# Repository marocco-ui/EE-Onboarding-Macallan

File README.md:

# Basic sensor interface PCB

EE subteam onboarding project. A 2-layer, 60 × 60 mm board that reads one 0 to 3.3 V analog sensor and one pushbutton with an ESP32-S3, powered and programmed over USB-C.

Calculations for the regulator, LED resistor, power budget, and trace widths are in `calculations.md`.

## Deliverables

| Item | File |
|---|---|
| Editable KiCad project | `kicad bike project.kicad_pro`, `.kicad_sch`, `.kicad_pcb`, `.kicad_dru` |
| Schematic PDF | `exports/schematic.pdf` |
| PCB layout PDF (one page per layer) | `exports/board_layout.pdf` |
| PCB layout screenshots | `board_preview.png`, `exports/board_top.png`, `exports/board_bottom.png` |
| Required calculations | `calculations.md` |
| Design decisions | this README |
| Checks | `ERC 3.rpt` (0 errors, 0 warnings), `DRC 4.rpt` (0 violations, 0 unconnected, schematic parity clean) |

## Block diagram

    USB-C (J1) --5 V--> AP7361C LDO (U2) --3.3 V--> ESP32-S3-WROOM-1 (U1)
        |                                               |
        +---- D+ / D- (native USB) ---------------------+
                                                         |
    Sensor connector (J2) --> divider + RC filter --> GPIO1 (ADC1_CH0)
    User button (SW1) --> pull-up + RC debounce --> GPIO4
    BOOT (SW2) --> GPIO0      RESET (SW3) --> EN

## Design decisions

**Microcontroller.** ESP32-S3-WROOM-1-N8 (8 MB flash, no PSRAM). It has native USB, so one USB-C port handles power and programming with no USB-to-serial chip. It also has an official KiCad symbol and footprint, which removes the risk of a hand-drawn footprint. The ESP32-C3-MINI-1 was the first choice, but KiCad's library has neither for it.

**Power.** 5 V comes from USB-C VBUS. CC1 and CC2 each get their own 5.1 kΩ pull-down (R8, R9), which tells a USB-C charger or port to turn on 5 V. The AP7361C LDO drops it to 3.3 V. An LDO fits because the load is under 0.5 A and the drop is only 1.7 V. See `calculations.md` for the heat check.

**Programming.** GPIO19 and GPIO20 are the chip's USB D− and D+. Both D+ pins on the USB-C connector are tied together, and both D− pins, so the cable works either way up. SW2 (BOOT) pulls GPIO0 low and SW3 (RESET) pulls EN low. Holding BOOT while tapping RESET forces download mode if USB auto-reset ever fails.

**Strapping pins.** GPIO0, GPIO3, GPIO45, and GPIO46 are read at power-up.
- GPIO0: internal pull-up plus R2 (10 kΩ). High = run the program, low = download mode.
- GPIO3: no internal pull, and the datasheet says it must not float. R3 (10 kΩ) pulls it up.
- GPIO45 and GPIO46: internal pull-downs are the correct levels, so both are left open.
None of these are used for the sensor or button.

**Analog input.** The ESP32-S3 ADC reads 0 to 3.1 V at its highest attenuation, so a 0 to 3.3 V sensor would clip at the top. A 10 kΩ / 30 kΩ divider scales 3.3 V to 2.475 V, leaving margin for resistor tolerance. A 100 nF cap at the ADC pin filters noise above about 212 Hz. The sensor uses GPIO1 (ADC1_CH0) because ADC2 is shared with Wi-Fi and its reads can fail while Wi-Fi runs.

**Digital input.** SW1 on GPIO4 is active low: 10 kΩ pull-up, button to ground, 100 nF for a 1 ms debounce. GPIO4 is not a strapping pin, so holding the button at power-up can't change the boot mode.

**Indicator.** D1 is a green power LED on the 3.3 V rail with a 680 Ω resistor (about 2 mA). It confirms the regulator works.

## Pin assignments (U1, ESP32-S3-WROOM-1)

| Module pin | Signal | Connection |
|---|---|---|
| 2 | 3V3 | LDO output, C4 + C5 local decoupling |
| 1, 40, 41 (pad) | GND | Ground plane |
| 3 | EN | R1 10 kΩ to 3V3, C6 1 uF to GND, SW3 to GND |
| 27 | IO0 | BOOT: R2 10 kΩ pull-up, SW2 to GND |
| 15 | IO3 | R3 10 kΩ pull-up (strapping) |
| 39 | IO1 | Sensor signal after divider (ADC1_CH0) |
| 4 | IO4 | User button SW1 |
| 13 | IO19 | USB D− |
| 14 | IO20 | USB D+ |
| All others | NC | No-connect flags in the schematic |

## Parts list

| Ref | Value / part | KiCad footprint | Purpose |
|---|---|---|---|
| U1 | ESP32-S3-WROOM-1-N8 | RF_Module:ESP32-S3-WROOM-1 | Microcontroller |
| U2 | AP7361C-33E-13 | Package_TO_SOT_SMD:SOT-223-3_TabPin2 | 5 V to 3.3 V LDO |
| J1 | USB-C, USB 2.0, 16-pin (GCT USB4105-GF-A) | Connector_USB:USB_C_Receptacle_GCT_USB4105-xx-A_16P_TopMnt_Horizontal | Power and programming |
| J2 | JST PH 3-pin (3V3, SIG, GND) | Connector_JST:JST_PH_B3B-PH-K_1x03_P2.00mm_Vertical | Sensor connector |
| SW1, SW2, SW3 | Tactile switch | Button_Switch_SMD:SW_SPST_TL3342 | USER, BOOT, RESET |
| D1 | LTST-C191KGKT green LED | LED_SMD:LED_0603_1608Metric | Power indicator |
| R1, R2, R3, R7 | 10 kΩ | Resistor_SMD:R_0603_1608Metric | EN, strapping, and button pull-ups |
| R4 | 680 Ω | Resistor_SMD:R_0603_1608Metric | LED current limit |
| R5 | 10 kΩ 1 % | Resistor_SMD:R_0603_1608Metric | Divider top |
| R6 | 30 kΩ 1 % | Resistor_SMD:R_0603_1608Metric | Divider bottom |
| R8, R9 | 5.1 kΩ | Resistor_SMD:R_0603_1608Metric | USB-C CC pull-downs |
| C1 | 4.7 uF 10 V X5R | Capacitor_SMD:C_0805_2012Metric | LDO input |
| C2 | 100 nF | Capacitor_SMD:C_0603_1608Metric | LDO input bypass |
| C3 | 10 uF 10 V X5R | Capacitor_SMD:C_0805_2012Metric | LDO output |
| C4 | 22 uF 10 V X5R | Capacitor_SMD:C_0805_2012Metric | Module 3V3 bulk |
| C5 | 100 nF | Capacitor_SMD:C_0603_1608Metric | Module 3V3 bypass |
| C6 | 1 uF | Capacitor_SMD:C_0603_1608Metric | EN delay |
| C7 | 100 nF | Capacitor_SMD:C_0603_1608Metric | ADC filter |
| C8 | 100 nF | Capacitor_SMD:C_0603_1608Metric | Button debounce |
| H1 to H4 | M3 mounting hole | MountingHole:MountingHole_3.2mm_M3 | Mounting |

## Board layout

60 × 60 mm, 2 layers, fully routed. KiCad 10 DRC: 0 violations, 0 unconnected items, 0 schematic-parity issues.

- **Module (U1).** Centered on the top edge, antenna 0.3 mm inside the edge so its silkscreen stays on the board. KiCad's footprint carries an antenna keep-out on both layers. It blocks tracks, vias, pours, and parts in a 6 mm strip along the top edge.
- **Mounting holes.** The bottom pair sits 4 mm from each edge. The top pair sits 10 mm down, because the antenna keep-out covers the normal corner spot.
- **USB-C (J1).** Bottom edge, positioned on the footprint's "PCB Edge" mark. CC pull-downs R8 and R9 sit either side.
- **Power.** The AP7361C (U2) sits lower left with its input facing J1. C1 and C2 are at the input and C3 at the output. The power LED (D1, R4) is on the left edge.
- **Module support.** C5 and C4 sit next to module pins 1 and 2 (GND, 3V3). The EN parts (R1, C6) and button parts (R7, C8) form a column on the left. RESET (SW3) and USER (SW1) are on the left edge.
- **Sensor.** Divider R5, R6, and C7 sit right next to GPIO1 (pin 39). J2 is on the right edge, silkscreen-labeled 3V3 / SIG / GND. BOOT (SW2) and its pull-up R2 are on the right side near GPIO0 (pin 27).
- **Ground.** The bottom layer has a GND pour, tied to the USB-C shield, J2 pin 3, and the module's ground-pad vias.
- **Silkscreen.** Every label sits clear of copper, other silkscreen, and the board edge. Pin labels on J2 read 3V3 / SIG / GND, and the connectors and buttons are labeled USB 5V, SENSOR, RESET, USER, and BOOT.

### Net classes

| Class | Nets | Track | Via |
|---|---|---|---|
| Power | VBUS, +3V3 | 0.4 mm | 0.8 mm / 0.4 mm drill |
| Ground | GND | 0.3 mm | 0.6 mm / 0.3 mm drill |
| Default | everything else | 0.2 mm | 0.6 mm / 0.3 mm drill |

The first plan was 0.5 mm for power. That width could not reach the USB-C VBUS pins or squeeze past the regulator and the passives beside the module, so the router left those connections open. 0.4 mm still carries 1.2 A by IPC-2221, 3.4 times the 357 mA worst case (see `calculations.md`).

### DRC exceptions (`kicad bike project.kicad_dru`)

Both come from the official KiCad land patterns, not from the layout:

1. U1's exposed ground pad has 0.2 mm thermal vias. The board minimum is 0.3 mm, so the rule allows 0.2 mm for pads inside U1 only.
2. J1's alignment holes sit 0.19 mm from its GND pads. The board minimum is 0.25 mm, so the rule allows 0.15 mm inside J1 only.

### Routing

Routed with Freerouting 2.1 and checked with KiCad's DRC after every attempt. Ten variants were tried with different widths, via costs, and strategies. The final board is the cleanest: 27 vias, about 345 mm of top-layer track, and nothing left unrouted.

Before the autorouter ran, three things were drawn by hand and locked:

1. **USB D+ and D−.** Both pairs of connector pads are tied on the top layer, D+ just above the pad row and D− just below it, with no vias. From there the two lines run up together and turn 45° as a parallel pair into module pins 13 and 14.
2. **One 3.3 V crossing under the USB pair.** 3.3 V has to reach R2, R3, and J2 on the right of the USB pair. It crosses on the bottom layer with a 3.9 mm hop just below the module, at right angles to the USB lines. That keeps the ground pour under the USB pair almost unbroken.
3. **Ground as a plane.** GND was given to the router as the bottom-layer plane, so every top-side ground pad drops straight down through its own via.

What is on the bottom layer besides the ground pour:

- the 3.3 V hop under the USB pair, plus a 3.3 V run under the module's bottom edge out to R2 and J2
- two short hops on the left edge for EN and BUTTON out to the RESET and USER switches

These come from the placement. The 3.3 V pads and the EN and BUTTON pads alternate down the column beside the module, so something has to cross. None of these tracks runs under the USB lines.

## How the scripts work

The schematic and the first board layout were generated by Python scripts rather than drawn by hand, then finished and checked in KiCad 10. Each script is short and does one job. They run on KiCad's Python module (`pcbnew`, KiCad 7 or later) and need Java 21 for Freerouting.

| Step | Script | What it does |
|---|---|---|
| 1. Read the library | `tools/sexp.py`, `tools/extract.py` | KiCad files are plain-text s-expressions (nested parentheses). These read the official symbol library and pull out each part's pins and their positions. |
| 2. Draw the schematic | `tools/gen_sch.py` | Places every symbol, draws a short wire from each pin to a net label or power symbol, adds no-connect flags, and writes `kicad bike project.kicad_sch`. |
| 3. Check the connections | `tools/check_net.py` | Has KiCad export the netlist, then compares every net against the intended connection table. It passed on all 14 nets before the file was used. |
| 4. Place the board | `tools/gen_pcb.py` | Uses KiCad's Python API to load each footprint, place it, link it to its schematic symbol, assign nets, draw the 60 × 60 mm outline, and add the bottom ground pour. |
| 5. Check the board | `tools/check_pcb.py` | Refills the ground pour and runs KiCad's DRC from Python. |
| 6. Route | `tools/routing/` | `preroute.py` draws and locks the USB pair and the 3.3 V hop. The board is exported to Specctra DSN, `mkdsn.py` makes width variants, and Freerouting routes each one. `ses_apply.py` loads a result back, and `evaluate.py` removes leftover stubs and duplicates, runs DRC, and scores it. `render.sh` makes the preview images. |
| 7. KiCad 10 cleanup | `tools/hide_desc.py`, `tools/verify_v10.py` | Hides the Description field that KiCad 10 added to every symbol, and confirms no pins moved after the library update. |

The Freerouting command used for each variant:

    java -jar freerouting-2.1.0.jar --gui.enabled=false -de board.dsn -do board.ses -mp 40

The silkscreen labels were then moved clear of copper with a short clearance search (`tools/routing/silk_labels.py`), and the final DRC (`DRC 4.rpt`) and ERC (`ERC 3.rpt`) were run in KiCad 10 itself.

### Learning resources

| Topic | Used in | Video |
|---|---|---|
| KiCad's Python API (`pcbnew`) | steps 4 to 6 | [The Python Whisperer Guide, KiCon 2019](https://www.youtube.com/watch?v=_zVJ96SdYrs) (Contextual Electronics) |
| Running DRC from Python | steps 5 and 6 | [Automated PCB Design Rule Validation Using KiCad Python API](https://www.youtube.com/watch?v=i7LbWIcxQyk) (Learning By Tutorials) |
| KiCad command line (`kicad-cli`) | step 3 | [KiCad 8: More powerful command line interface](https://www.youtube.com/watch?v=j4sTVdC6o-U) (Tech Explorations) |
| Installing Freerouting | step 6 | [KiCad 8.0 Autorouter Installation in Under 4 Minutes](https://www.youtube.com/watch?v=zKeVWIWrCuI) (Stuart Patterson) |
| DSN export and SES import | step 6 | [How to Autoroute in KiCad 7.0 with FreeRouting](https://www.youtube.com/watch?v=duw2oUJPp9w) (Pcb Cupid) |
| Cleaning up after the autorouter | step 6 | [How to install and use KiCad FreeRouting, incl. manual cleanup and DRC](https://www.youtube.com/watch?v=ESrHILARL7Y) (eRCaGuy) |
| Custom DRC rules (`.kicad_dru`) | DRC exceptions | [Level up Your Custom Rules, KiCon Asia 2023](https://www.youtube.com/watch?v=_kk5-yVSDWk) (KiCad) |

Reference docs: [KiCad schematic file format](https://dev-docs.kicad.org/en/file-formats/sexpr-schematic/) (step 2) and [Freerouting command-line arguments](https://github.com/freerouting/freerouting/blob/master/docs/command_line_arguments.md) (step 6).

KiCad 10 renamed the USB-C shield pin from S1 to SH, so the J1 footprint's shield pads use SH to match.

## Open items

- Add the sensor's own current to the power budget once a sensor is chosen.
- Optional: USB ESD protection (e.g. USBLC6-2SC6) and a 500 mA PTC fuse on VBUS.
- The D− pad tie on J1 runs 0.3 mm past the pad row, just under the edge of the connector body. Check the GCT USB4105 drawing for any copper keep-out there before ordering boards.

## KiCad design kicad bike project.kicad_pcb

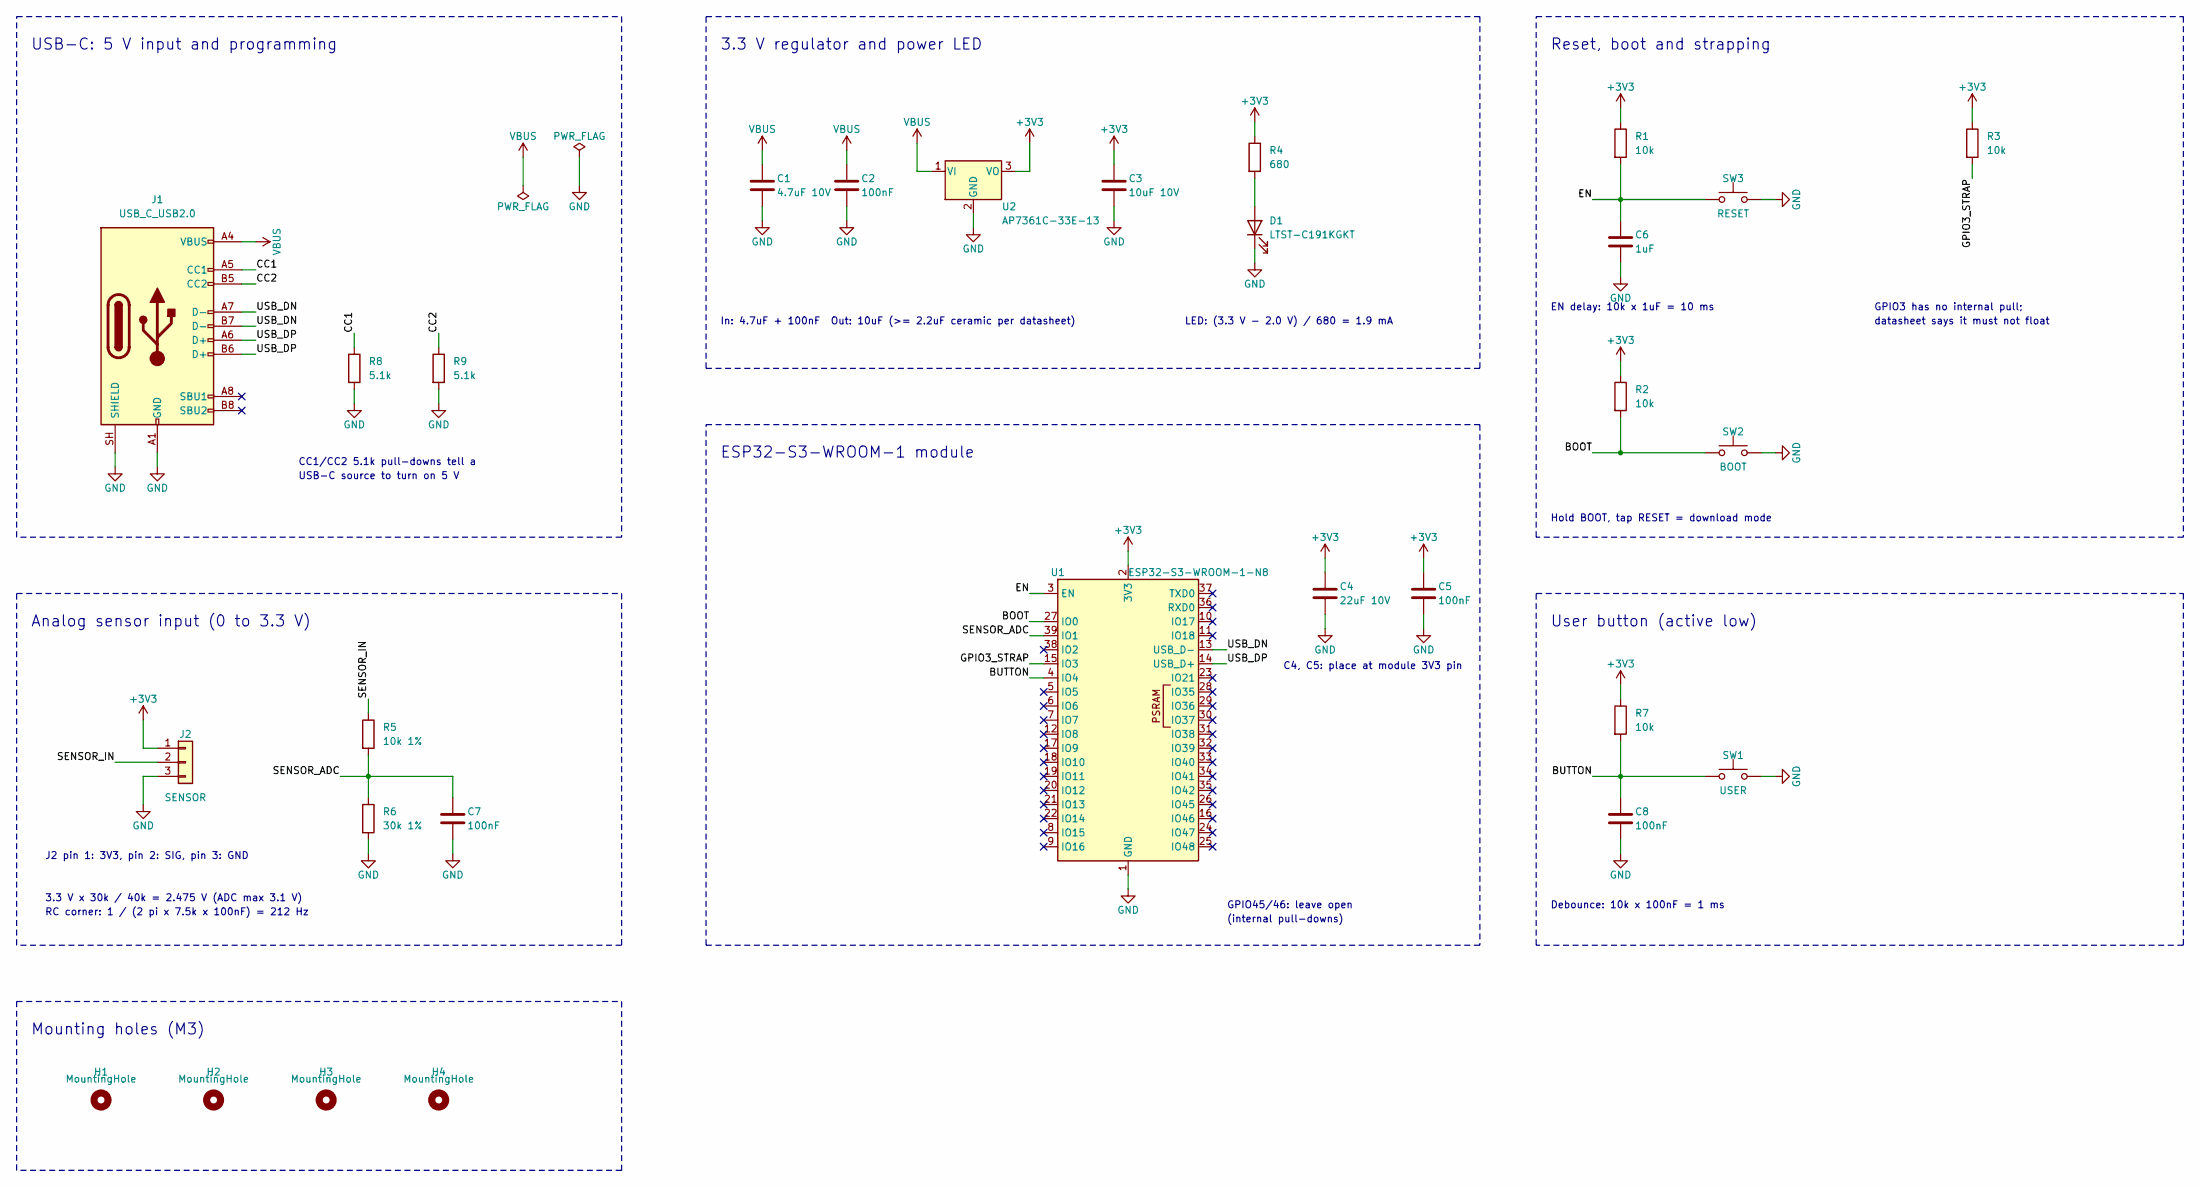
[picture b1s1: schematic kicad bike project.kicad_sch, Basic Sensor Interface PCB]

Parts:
C1: 4.7uF 10V; C_0805_2012Metric
C2, C5, C7, C8: 100nF; C_0603_1608Metric
C3: 10uF 10V; C_0805_2012Metric
C4: 22uF 10V; C_0805_2012Metric
C6: 1uF; C_0603_1608Metric
D1: LTST-C191KGKT; LED_0603_1608Metric
H1, H2, H3, H4: MountingHole; MountingHole_3.2mm_M3
J1: USB_C_USB2.0; USB_C_Receptacle_GCT_USB4105-xx-A_16P_TopMnt_Horizontal; MPN GCT USB4105-GF-A
J2: SENSOR; JST_PH_B3B-PH-K_1x03_P2.00mm_Vertical
R1, R2, R3, R7: 10k; R_0603_1608Metric
R4: 680; R_0603_1608Metric
R5: 10k 1%; R_0603_1608Metric
R6: 30k 1%; R_0603_1608Metric
R8, R9: 5.1k; R_0603_1608Metric
SW1: USER; SW_SPST_TL3342
SW2: BOOT; SW_SPST_TL3342
SW3: RESET; SW_SPST_TL3342
U1: ESP32-S3-WROOM-1-N8; ESP32-S3-WROOM-1
U2: AP7361C-33E-13; SOT-223-3_TabPin2

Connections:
+3V3: C3.1, C4.1, C5.1, J2.1, R1.1, R2.1, R3.1, R4.1, R7.1, U1.2 (3V3), U2.3 (VO)
/BOOT: R2.2, SW2.1, U1.27 (IO0)
/BUTTON: C8.1, R7.2, SW1.1, U1.4 (IO4)
/CC1: J1.A5 (CC1), R8.1
/CC2: J1.B5 (CC2), R9.1
/EN: C6.1, R1.2, SW3.1, U1.3 (EN)
/GPIO3_STRAP: R3.2, U1.15 (IO3)
/SENSOR_ADC: C7.1, R5.2, R6.1, U1.39 (IO1)
/SENSOR_IN: J2.2, R5.1
/USB_DN: J1.A7 (D-), J1.B7 (D-), U1.13 (USB_D-)
/USB_DP: J1.A6 (D+), J1.B6 (D+), U1.14 (USB_D+)
GND: C1.2, C2.2, C3.2, C4.2, C5.2, C6.2, C7.2, C8.2, D1.1 (K), J1.A1 (GND), J1.A12 (GND), J1.B1 (GND), J1.B12 (GND), J1.SH (SHIELD), J2.3, R6.2, R8.2, R9.2, SW1.2, SW2.2, SW3.2, U1.1 (GND), U1.40 (GND), U1.41 (GND), U2.2 (GND)
unnamed: D1.2 (A), R4.2
VBUS: C1.1, C2.1, J1.A4 (VBUS), J1.A9 (VBUS), J1.B4 (VBUS), J1.B9 (VBUS), U2.1 (VI)

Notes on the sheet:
EN delay: 10k x 1uF = 10 ms
Analog sensor input (0 to 3.3 V)
Hold BOOT, tap RESET = download mode
USB-C: 5 V input and programming
User button (active low)
datasheet says it must not float
J2 pin 1: 3V3, pin 2: SIG, pin 3: GND
GPIO45/46: leave open
CC1/CC2 5.1k pull-downs tell a
Reset, boot and strapping
Debounce: 10k x 100nF = 1 ms
In: 4.7uF + 100nF Out: 10uF (>= 2.2uF ceramic per datasheet)
LED: (3.3 V - 2.0 V) / 680 = 1.9 mA
Mounting holes (M3)
GPIO3 has no internal pull;
USB-C source to turn on 5 V
ESP32-S3-WROOM-1 module
3.3 V regulator and power LED
3.3 V x 30k / 40k = 2.475 V (ADC max 3.1 V)
(internal pull-downs)
RC corner: 1 / (2 pi x 7.5k x 100nF) = 212 Hz
C4, C5: place at module 3V3 pin

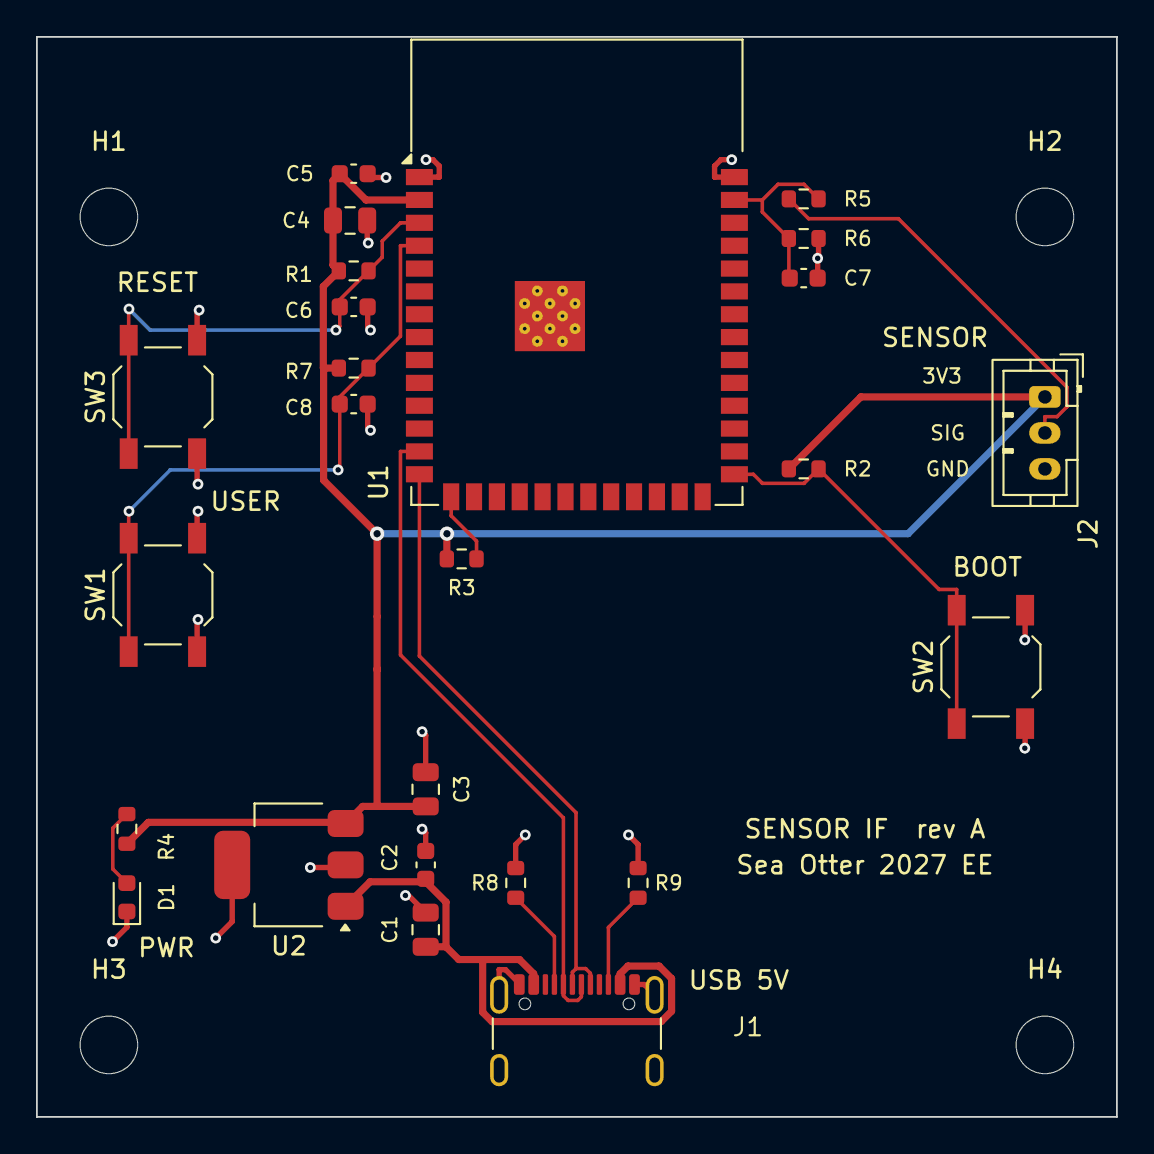
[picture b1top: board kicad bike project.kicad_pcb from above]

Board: 2 copper layers, 60.0 x 60.0 mm, 29 parts (0 on the bottom side), 14 nets.
